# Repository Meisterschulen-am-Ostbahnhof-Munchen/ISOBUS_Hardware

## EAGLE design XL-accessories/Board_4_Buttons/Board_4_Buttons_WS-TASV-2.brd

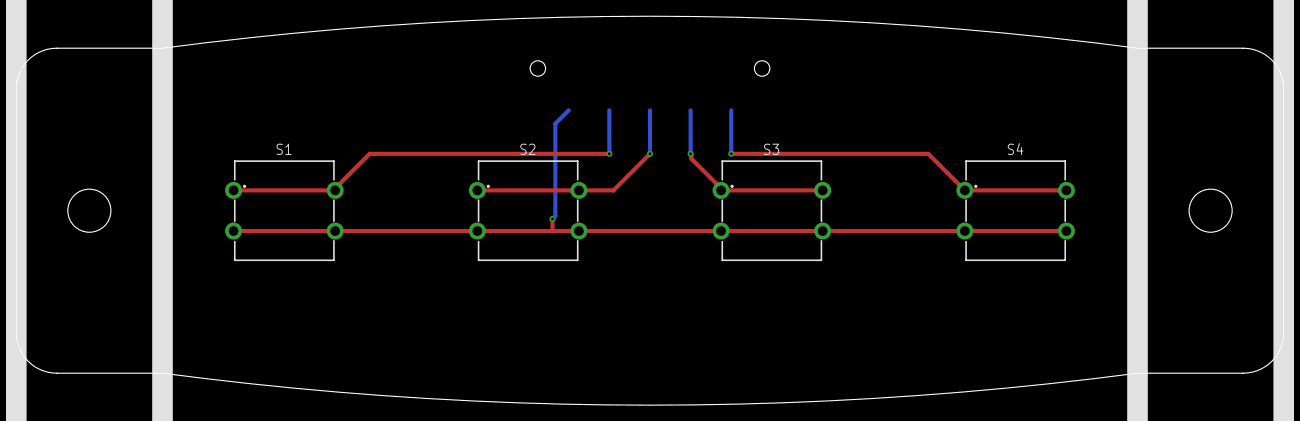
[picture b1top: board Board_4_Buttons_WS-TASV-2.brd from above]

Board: 2 copper layers, 156.0 x 47.9 mm, 5 parts (1 on the bottom side), 5 nets.

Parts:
J1: 691709710305
S1, S2, S3, S4: 430162073826; 4304X60437X6

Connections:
unnamed: J1.1, S1.3, S1.4, S2.3, S2.4, S3.3, S3.4, S4.3, S4.4
unnamed: J1.2, S1.1, S1.2
unnamed: J1.3, S2.1, S2.2
unnamed: J1.4, S3.1, S3.2
unnamed: J1.5, S4.1, S4.2

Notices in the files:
parts and their libraries:
Wurth_Connectors_WR-TBL Rising Cage Clam: Copyright: Würth Elektronik
